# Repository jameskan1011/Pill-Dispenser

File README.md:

# Pill-Dispenser
Pill Dispensir with onboard settings that let you customize reminders for your meds.
<br />• Can be stack for multiple types of pill
<br />• Buzzer alert
<br />• Pill drop count
<br />• Customize time and quantities for meds.

https://github.com/jameskan1011/Pill-Dispenser/assets/66528008/c5491cce-084c-414e-90f5-08d18c687c19

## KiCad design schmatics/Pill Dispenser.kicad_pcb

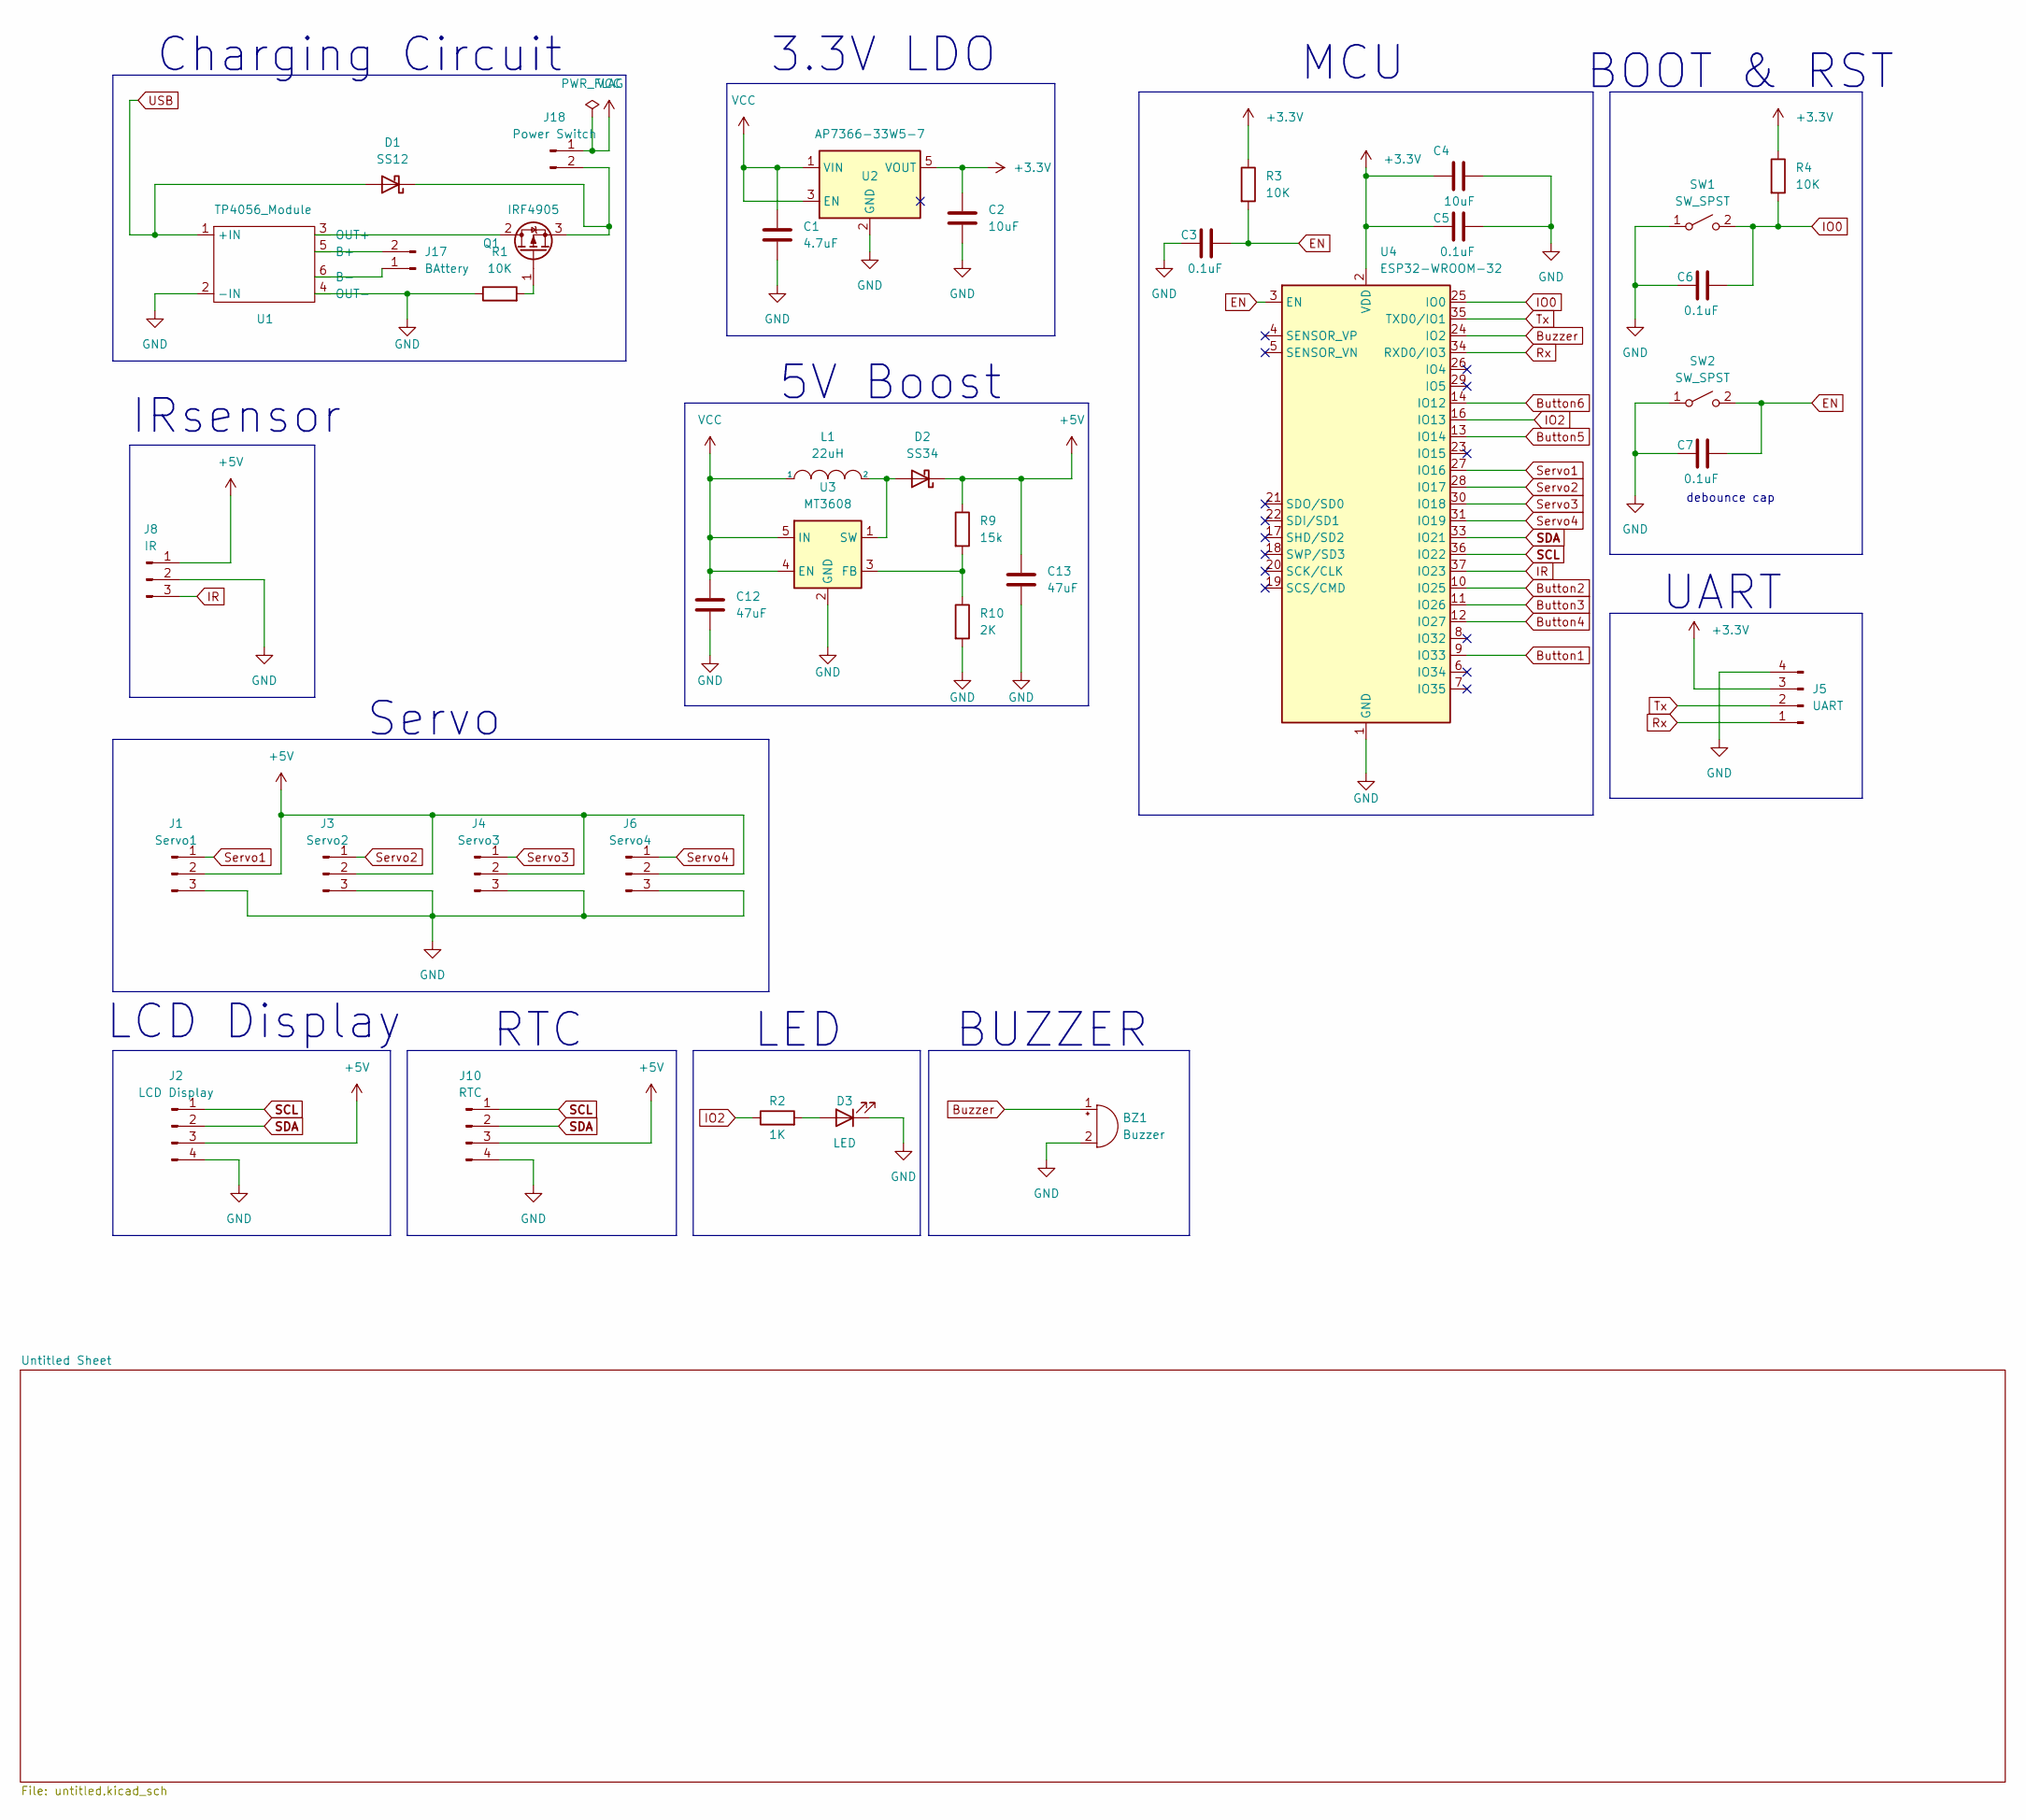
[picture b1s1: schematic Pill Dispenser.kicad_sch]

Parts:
BZ1: Buzzer; Buzzer_12x9.5RM7.6
C1: 4.7uF; C_0805_2012Metric
C2, C4: 10uF; C_0805_2012Metric
C3, C5, C6, C7: 0.1uF; C_0805_2012Metric
C12, C13: 47uF; C_0805_2012Metric
D1: SS12; D_SMA
D2: SS34; D_SMA
D3: LED; LED_0805_2012Metric
J1: Servo1; PinHeader_1x03_P2.54mm_Vertical
J2: LCD Display; PinHeader_1x04_P2.54mm_Vertical
J3: Servo2; PinHeader_1x03_P2.54mm_Vertical
J4: Servo3; PinHeader_1x03_P2.54mm_Vertical
J5: UART; PinHeader_1x04_P2.54mm_Vertical
J6: Servo4; PinHeader_1x03_P2.54mm_Vertical
J8: IR; PinHeader_1x03_P2.54mm_Vertical
J10: RTC; PinHeader_1x04_P2.54mm_Vertical
J17: BAttery; PinHeader_1x02_P2.54mm_Vertical
J18: Power Switch; PinHeader_1x02_P2.54mm_Vertical
L1: 22uH; L_7.3x7.3_H4.5
Q1: IRF4905; TO-220-3_Vertical
R1, R3, R4: 10K; R_0805_2012Metric_Pad1.20x1.40mm_HandSolder
R2: 1K; R_0805_2012Metric_Pad1.20x1.40mm_HandSolder
R9: 15k; R_0805_2012Metric_Pad1.20x1.40mm_HandSolder
R10: 2K; R_0805_2012Metric_Pad1.20x1.40mm_HandSolder
SW1, SW2: SW_SPST; SW_SPST_TL3305A
U1: TP4056_Module
U2: AP7366-33W5-7; SOT-23-5_HandSoldering
U3: MT3608; SOT-23-6
U4: ESP32-WROOM-32

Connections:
+3V3: C2.1, C4.1, C5.1, J5.3, R3.1, R4.1, U2.5 (VOUT), U4.2 (VDD)
+5V: C13.1, D2.1 (K), J1.2, J2.3, J3.2, J4.2, J6.2, J8.1, J10.3, R9.1; also elsewhere on the board
Button1: U4.9 (IO33); also elsewhere on the board
Button2: U4.10 (IO25); also elsewhere on the board
Button3: U4.11 (IO26); also elsewhere on the board
Button4: U4.12 (IO27); also elsewhere on the board
Button5: U4.13 (IO14); also elsewhere on the board
Button6: U4.14 (IO12); also elsewhere on the board
Buzzer: BZ1.1 (-), U4.24 (IO2)
EN: C3.2, C7.2, R3.2, SW2.2 (B), U4.3 (EN)
GND: BZ1.2 (+), C1.2, C2.2, C3.1, C4.2, C5.2, C6.1, C7.1, C12.2, C13.2, D3.1 (K), J1.3, J2.4, J3.3, J4.3, J5.4, J6.3, J8.2, J10.4, R1.1, R10.2, SW1.1 (A), SW2.1 (A), U1.2 (-IN), U1.4 (OUT-), U2.2 (GND), U3.2 (GND), U4.1 (GND), U4.15 (GND), U4.38 (GND), U4.39 (GND); also elsewhere on the board
IO0: C6.2, R4.2, SW1.2 (B), U4.25 (IO0)
IO2: R2.1, U4.16 (IO13)
IR: J8.3, U4.37 (IO23)
unnamed: D1.1 (K), J18.2, Q1.3 (S)
unnamed: D2.2 (A), L1.2, U3.1 (SW)
unnamed: D3.2 (A), R2.2
unnamed: J17.1, U1.6 (B-)
unnamed: J17.2, U1.5 (B+)
unnamed: Q1.1 (G), R1.2
unnamed: Q1.2 (D), U1.3 (OUT+)
unnamed: R9.2, R10.1, U3.3 (FB)
Rx: J5.1, U4.34 (RXD0/IO3)
SCL: J2.1, J10.1, U4.36 (IO22)
SDA: J2.2, J10.2, U4.33 (IO21)
Servo1: J1.1, U4.27 (IO16)
Servo2: J3.1, U4.28 (IO17)
Servo3: J4.1, U4.30 (IO18)
Servo4: J6.1, U4.31 (IO19)
Tx: J5.2, U4.35 (TXD0/IO1)
USB: D1.2 (A), U1.1 (+IN)
VCC: C1.1, C12.1, J18.1, L1.1, U2.1 (VIN), U2.3 (EN), U3.4 (EN), U3.5 (IN)

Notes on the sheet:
Charging Circuit
Servo
MCU
BOOT & RST
3.3V LDO
LCD Display
5V Boost
BUZZER
debounce cap
LED
UART
RTC
IRsensor

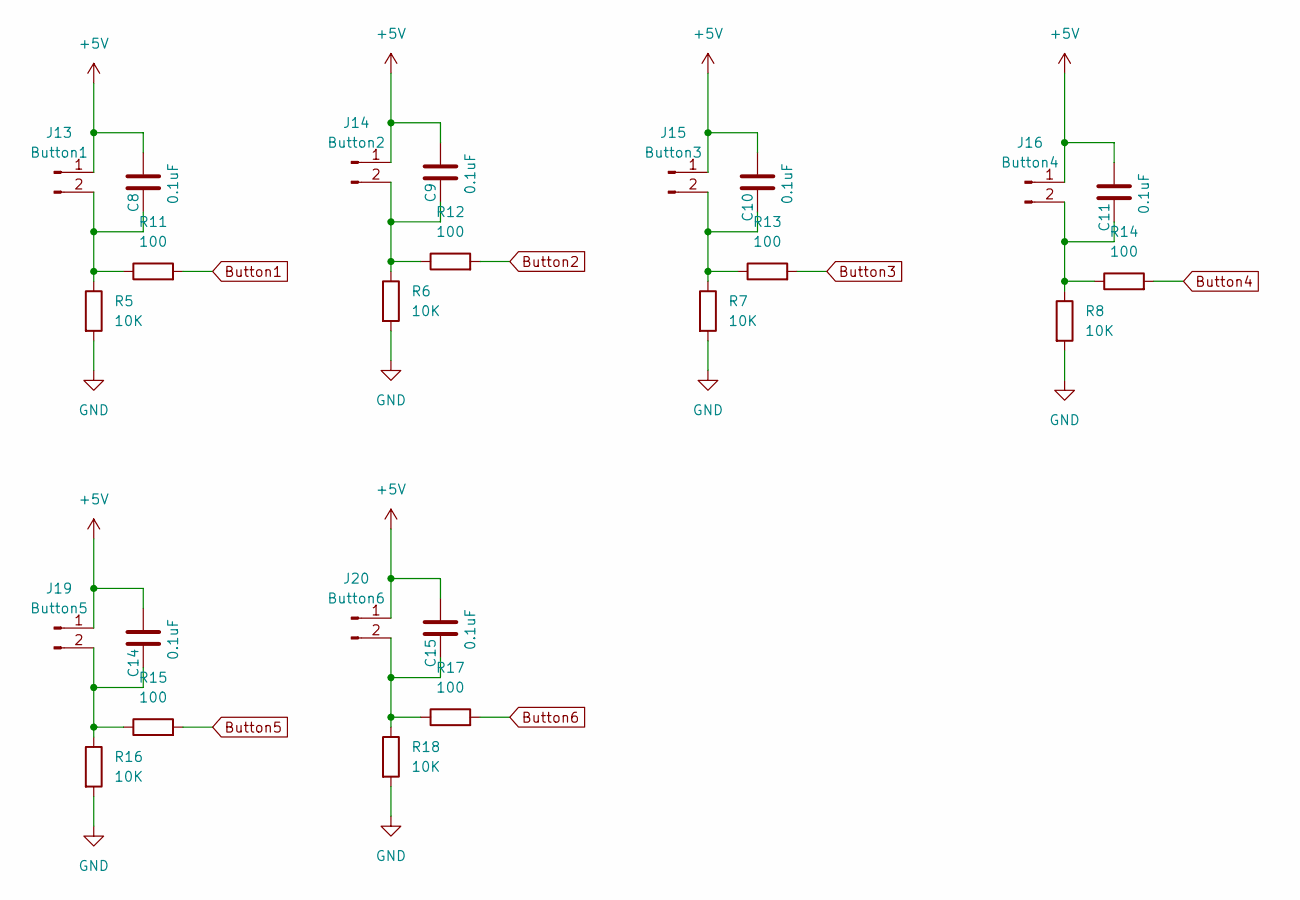
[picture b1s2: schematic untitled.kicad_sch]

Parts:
C8, C9, C10, C11, C14, C15: 0.1uF; C_0805_2012Metric
J13: Button1; PinHeader_1x02_P2.54mm_Vertical
J14: Button2; PinHeader_1x02_P2.54mm_Vertical
J15: Button3; PinHeader_1x02_P2.54mm_Vertical
J16: Button4; PinHeader_1x02_P2.54mm_Vertical
J19: Button5; PinHeader_1x02_P2.54mm_Vertical
J20: Button6; PinHeader_1x02_P2.54mm_Vertical
R5, R6, R7, R8, R16, R18: 10K; R_0805_2012Metric_Pad1.20x1.40mm_HandSolder
R11, R12, R13, R14, R15, R17: 100; R_0805_2012Metric_Pad1.20x1.40mm_HandSolder

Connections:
+5V: C8.2, C9.2, C10.2, C11.2, C14.2, C15.2, J13.1, J14.1, J15.1, J16.1, J19.1, J20.1; also elsewhere on the board
Button1: R11.2; also elsewhere on the board
Button2: R12.2; also elsewhere on the board
Button3: R13.2; also elsewhere on the board
Button4: R14.2; also elsewhere on the board
Button5: R15.2; also elsewhere on the board
Button6: R17.2; also elsewhere on the board
GND: R5.2, R6.2, R7.2, R8.2, R16.2, R18.2; also elsewhere on the board
unnamed: C8.1, J13.2, R5.1, R11.1
unnamed: C9.1, J14.2, R6.1, R12.1
unnamed: C10.1, J15.2, R7.1, R13.1
unnamed: C11.1, J16.2, R8.1, R14.1
unnamed: C14.1, J19.2, R15.1, R16.1
unnamed: C15.1, J20.2, R17.1, R18.1

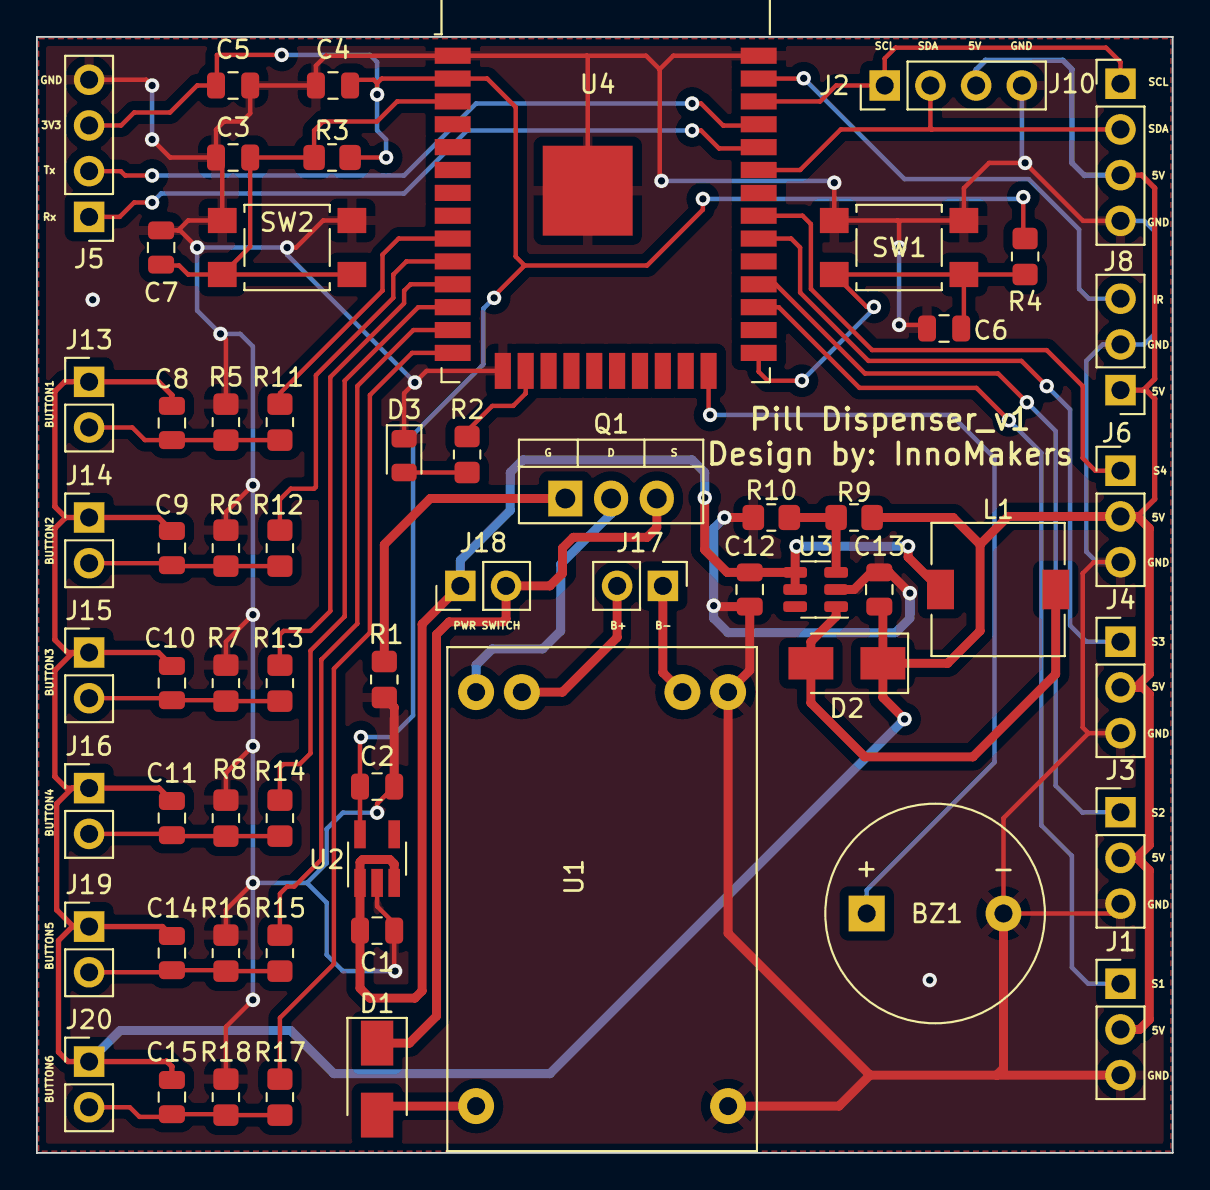
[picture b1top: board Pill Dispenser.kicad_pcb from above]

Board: 2 copper layers, 63.1 x 62.0 mm, 61 parts (0 on the bottom side), 38 nets.

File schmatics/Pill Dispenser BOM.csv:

Source:,C:\Users\KAN CHANG FEI\Documents\KiCad\6.0\projects\Pill Dispenser\Pill Dispenser\Pill Dispenser.kicad_sch,,,,,,,
Date:,4/19/2023 23:44,,,,,,,
Tool:,Eeschema (6.0.5),,,,,,,
Generator:,C:\Program Files\KiCad\6.0\bin\scripting\plugins/bom_csv_grouped_by_value.py,,,,,,,
Component Count:,61,,,,,,,
,,,,,,,,
Collated Components:,,,,,,,,
,,,,,,,,
Item,Qty,Reference(s),Value,Unit Price,Cost,LibPart,Footprint,Datasheet
1,1,BZ1,Buzzer,,,Device:Buzzer,Buzzer_Beeper:Buzzer_12x9.5RM7.6,~
2,1,C1,4.7uF,,,Device:C,Capacitor_SMD:C_0805_2012Metric,~
3,2,"C2, C4",10uF,,,Device:C,Capacitor_SMD:C_0805_2012Metric,~
4,10,"C3, C5, C6, C7, C8, C9, C10, C11, C14, C15",0.1uF,,,Device:C,Capacitor_SMD:C_0805_2012Metric,~
5,2,"C12, C13",47uF,,,Device:C,Capacitor_SMD:C_0805_2012Metric,~
6,1,D1,SS12,,,Device:D_Schottky,Diode_SMD:D_SMA,~
7,1,D2,SS34,,,Device:D_Schottky,Diode_SMD:D_SMA,~
8,1,D3,LED,,,Device:LED,LED_SMD:LED_0805_2012Metric,~
9,1,J1,Servo1,,,Connector:Conn_01x03_Male,Connector_PinHeader_2.54mm:PinHeader_1x03_P2.54mm_Vertical,~
10,1,J2,LCD Display,,,Connector:Conn_01x04_Male,Connector_PinHeader_2.54mm:PinHeader_1x04_P2.54mm_Vertical,~
11,1,J3,Servo2,,,Connector:Conn_01x03_Male,Connector_PinHeader_2.54mm:PinHeader_1x03_P2.54mm_Vertical,~
12,1,J4,Servo3,,,Connector:Conn_01x03_Male,Connector_PinHeader_2.54mm:PinHeader_1x03_P2.54mm_Vertical,~
13,1,J5,UART,,,Connector:Conn_01x04_Male,Connector_PinHeader_2.54mm:PinHeader_1x04_P2.54mm_Vertical,~
14,1,J6,Servo4,,,Connector:Conn_01x03_Male,Connector_PinHeader_2.54mm:PinHeader_1x03_P2.54mm_Vertical,~
15,1,J8,IR,,,Connector:Conn_01x03_Male,Connector_PinHeader_2.54mm:PinHeader_1x03_P2.54mm_Vertical,~
16,1,J10,RTC,12.5,12.5,Connector:Conn_01x04_Male,Connector_PinHeader_2.54mm:PinHeader_1x04_P2.54mm_Vertical,~
17,1,J13,Button1,,,Connector:Conn_01x02_Male,Connector_PinHeader_2.54mm:PinHeader_1x02_P2.54mm_Vertical,~
18,1,J14,Button2,,,Connector:Conn_01x02_Male,Connector_PinHeader_2.54mm:PinHeader_1x02_P2.54mm_Vertical,~
19,1,J15,Button3,,,Connector:Conn_01x02_Male,Connector_PinHeader_2.54mm:PinHeader_1x02_P2.54mm_Vertical,~
20,1,J16,Button4,,,Connector:Conn_01x02_Male,Connector_PinHeader_2.54mm:PinHeader_1x02_P2.54mm_Vertical,~
21,1,J17,BAttery,,,Connector:Conn_01x02_Male,Connector_PinHeader_2.54mm:PinHeader_1x02_P2.54mm_Vertical,~
22,1,J18,Power Switch,,,Connector:Conn_01x02_Male,Connector_PinHeader_2.54mm:PinHeader_1x02_P2.54mm_Vertical,~
23,1,J19,Button5,,,Connector:Conn_01x02_Male,Connector_PinHeader_2.54mm:PinHeader_1x02_P2.54mm_Vertical,~
24,1,J20,Button6,,,Connector:Conn_01x02_Male,Connector_PinHeader_2.54mm:PinHeader_1x02_P2.54mm_Vertical,~
25,1,L1,22uH,,,pspice:INDUCTOR,Inductor_SMD:L_7.3x7.3_H4.5,~
26,1,Q1,IRF4905,,,Transistor_FET:IRF9540N,Package_TO_SOT_THT:TO-220-3_Vertical,http://www.irf.com/product-info/datasheets/data/irf9540n.pdf
27,9,"R1, R3, R4, R5, R6, R7, R8, R16, R18",10K,,,Device:R,Resistor_SMD:R_0805_2012Metric_Pad1.20x1.40mm_HandSolder,~
28,1,R2,1K,,,Device:R,Resistor_SMD:R_0805_2012Metric_Pad1.20x1.40mm_HandSolder,~
29,1,R9,14.7K,,,Device:R,Resistor_SMD:R_0805_2012Metric_Pad1.20x1.40mm_HandSolder,~
30,1,R10,2K,,,Device:R,Resistor_SMD:R_0805_2012Metric_Pad1.20x1.40mm_HandSolder,~
31,6,"R11, R12, R13, R14, R15, R17",100,,,Device:R,Resistor_SMD:R_0805_2012Metric_Pad1.20x1.40mm_HandSolder,~
32,2,"SW1, SW2",SW_SPST,,,Switch:SW_SPST,Button_Switch_SMD:SW_SPST_TL3305A,~
33,1,U1,TP4056_Module,,,My_Design:TP4056_Module,My_Design:TP4056_Module,
34,1,U2,AP7366-33W5-7,,,Regulator_Linear:MIC5504-3.3YM5,Package_TO_SOT_SMD:SOT-23-5_HandSoldering,http://ww1.microchip.com/downloads/en/DeviceDoc/MIC550X.pdf
35,1,U3,MT3608,,,Regulator_Switching:MT3608,Package_TO_SOT_SMD:SOT-23-6,https://www.olimex.com/Products/Breadboarding/BB-PWR-3608/re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
36,1,U4,ESP32-WROOM-32,10,10,RF_Module:ESP32-WROOM-32,RF_Module:ESP32-WROOM-32,https://www.espressif.com/sites/default/files/documentation/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
